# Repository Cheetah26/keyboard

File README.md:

# keyboard
My fully custom split keyboard

## Features
- 40 key split layout
- dual rp2040 microcontrollers
- [kmk](http://kmkfw.io) firmware
- stenography layer for [plover](http://www.openstenoproject.org/)
- 3d printed base

## Background / design 
After years of wanting an ergonomic split keyboard but never seeing one that perfectly matched what I imagined in my mind, I decided to design and build my own!

I started completely from scratch by putting my hand on a sheet of paper and just seeing where my fingers liked to be. From there I made a layout based on where keys could actually go, and iterated until things really felt right.

I laid out the PCB according to this design, ordered all the parts, and anxiously waited to find out what I messed up. Since this was my first time designing a PCB, fist time programming a microcontroller, and first big soldering project, I 100% expected something to go wrong. To my surprise, the only issue was that I forgot to account for the size of the jack connecting each half. After a little sanding, everything went together perfectly and now I couldn't be happier with it.

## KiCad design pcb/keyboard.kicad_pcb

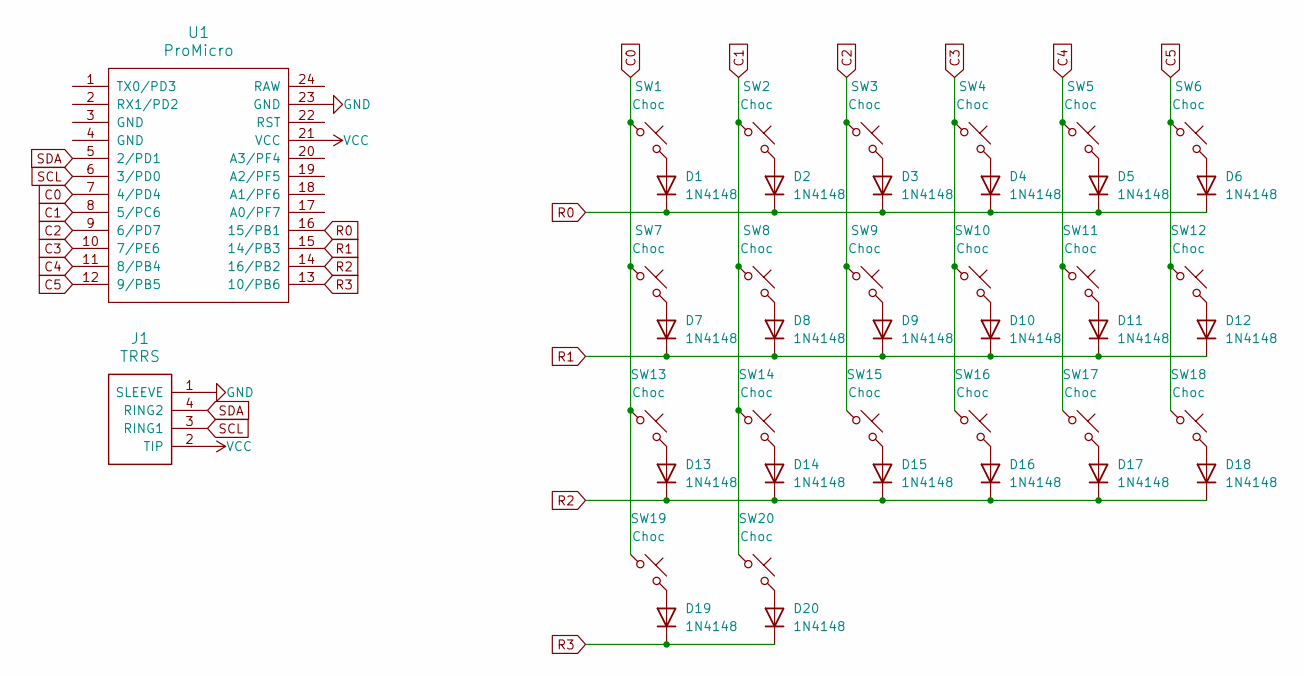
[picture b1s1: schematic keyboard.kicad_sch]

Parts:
D1, D2, D3, D4, D5, D6, D7, D8, D9, D10, D11, D12, D13, D14, D15, D16, D17, D18, D19, D20: 1N4148; Diode
J1: TRRS; PJ320-A_TRRS
SW1, SW2, SW3, SW4, SW5, SW6, SW7, SW8, SW9, SW10, SW11, SW12, SW13, SW14, SW15, SW16, SW17, SW18, SW19, SW20: Choc; Kailh_socket_PG1350_optional_reversible_outline
U1: ProMicro

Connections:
C0: SW1.1, SW7.1, SW13.1, SW19.1, U1.7 (4/PD4)
C1: SW2.1, SW8.1, SW14.1, SW20.1, U1.8 (5/PC6)
C2: SW3.1, SW9.1, SW15.1, U1.9 (6/PD7)
C3: SW4.1, SW10.1, SW16.1, U1.10 (7/PE6)
C4: SW5.1, SW11.1, SW17.1, U1.11 (8/PB4)
C5: SW6.1, SW12.1, SW18.1, U1.12 (9/PB5)
GND: J1.1 (SLEEVE), U1.23 (GND)
unnamed: D1.2 (A), SW1.2
unnamed: D2.2 (A), SW2.2
unnamed: D3.2 (A), SW3.2
unnamed: D4.2 (A), SW4.2
unnamed: D5.2 (A), SW5.2
unnamed: D6.2 (A), SW6.2
unnamed: D7.2 (A), SW7.2
unnamed: D8.2 (A), SW8.2
unnamed: D9.2 (A), SW9.2
unnamed: D10.2 (A), SW10.2
unnamed: D11.2 (A), SW11.2
unnamed: D12.2 (A), SW12.2
unnamed: D13.2 (A), SW13.2
unnamed: D14.2 (A), SW14.2
unnamed: D15.2 (A), SW15.2
unnamed: D16.2 (A), SW16.2
unnamed: D17.2 (A), SW17.2
unnamed: D18.2 (A), SW18.2
unnamed: D19.2 (A), SW19.2
unnamed: D20.2 (A), SW20.2
R0: D1.1 (K), D2.1 (K), D3.1 (K), D4.1 (K), D5.1 (K), D6.1 (K), U1.16 (15/PB1)
R1: D7.1 (K), D8.1 (K), D9.1 (K), D10.1 (K), D11.1 (K), D12.1 (K), U1.15 (14/PB3)
R2: D13.1 (K), D14.1 (K), D15.1 (K), D16.1 (K), D17.1 (K), D18.1 (K), U1.14 (16/PB2)
R3: D19.1 (K), D20.1 (K), U1.13 (10/PB6)
SCL: J1.3 (RING1), U1.6 (3/PD0)
SDA: J1.4 (RING2), U1.5 (2/PD1)
VCC: J1.2 (TIP), U1.21 (VCC)

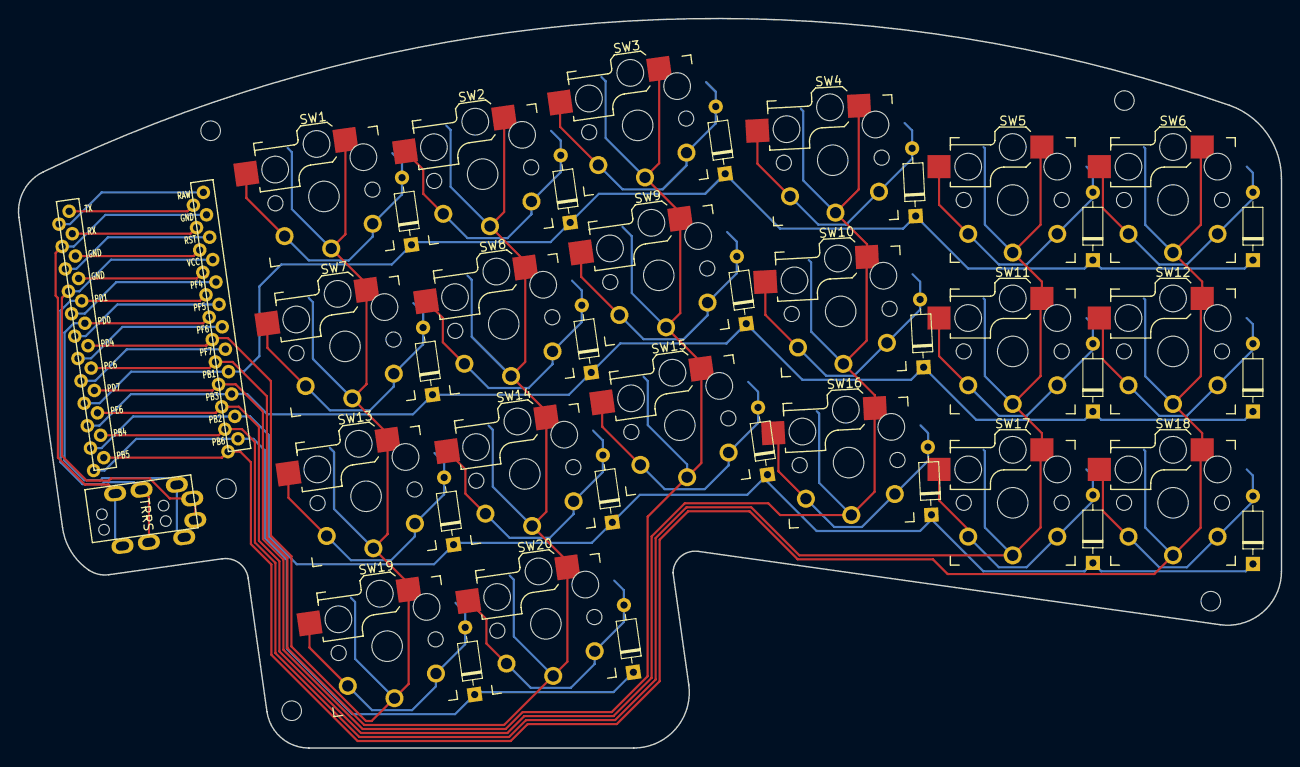
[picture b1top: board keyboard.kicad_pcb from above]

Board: 2 copper layers, 141.8 x 81.9 mm, 42 parts (0 on the bottom side), 34 nets.

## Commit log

2024-02-02 Add files
2024-02-02 Write the readme
2024-02-02 Add base files
2024-02-02 correct readme
